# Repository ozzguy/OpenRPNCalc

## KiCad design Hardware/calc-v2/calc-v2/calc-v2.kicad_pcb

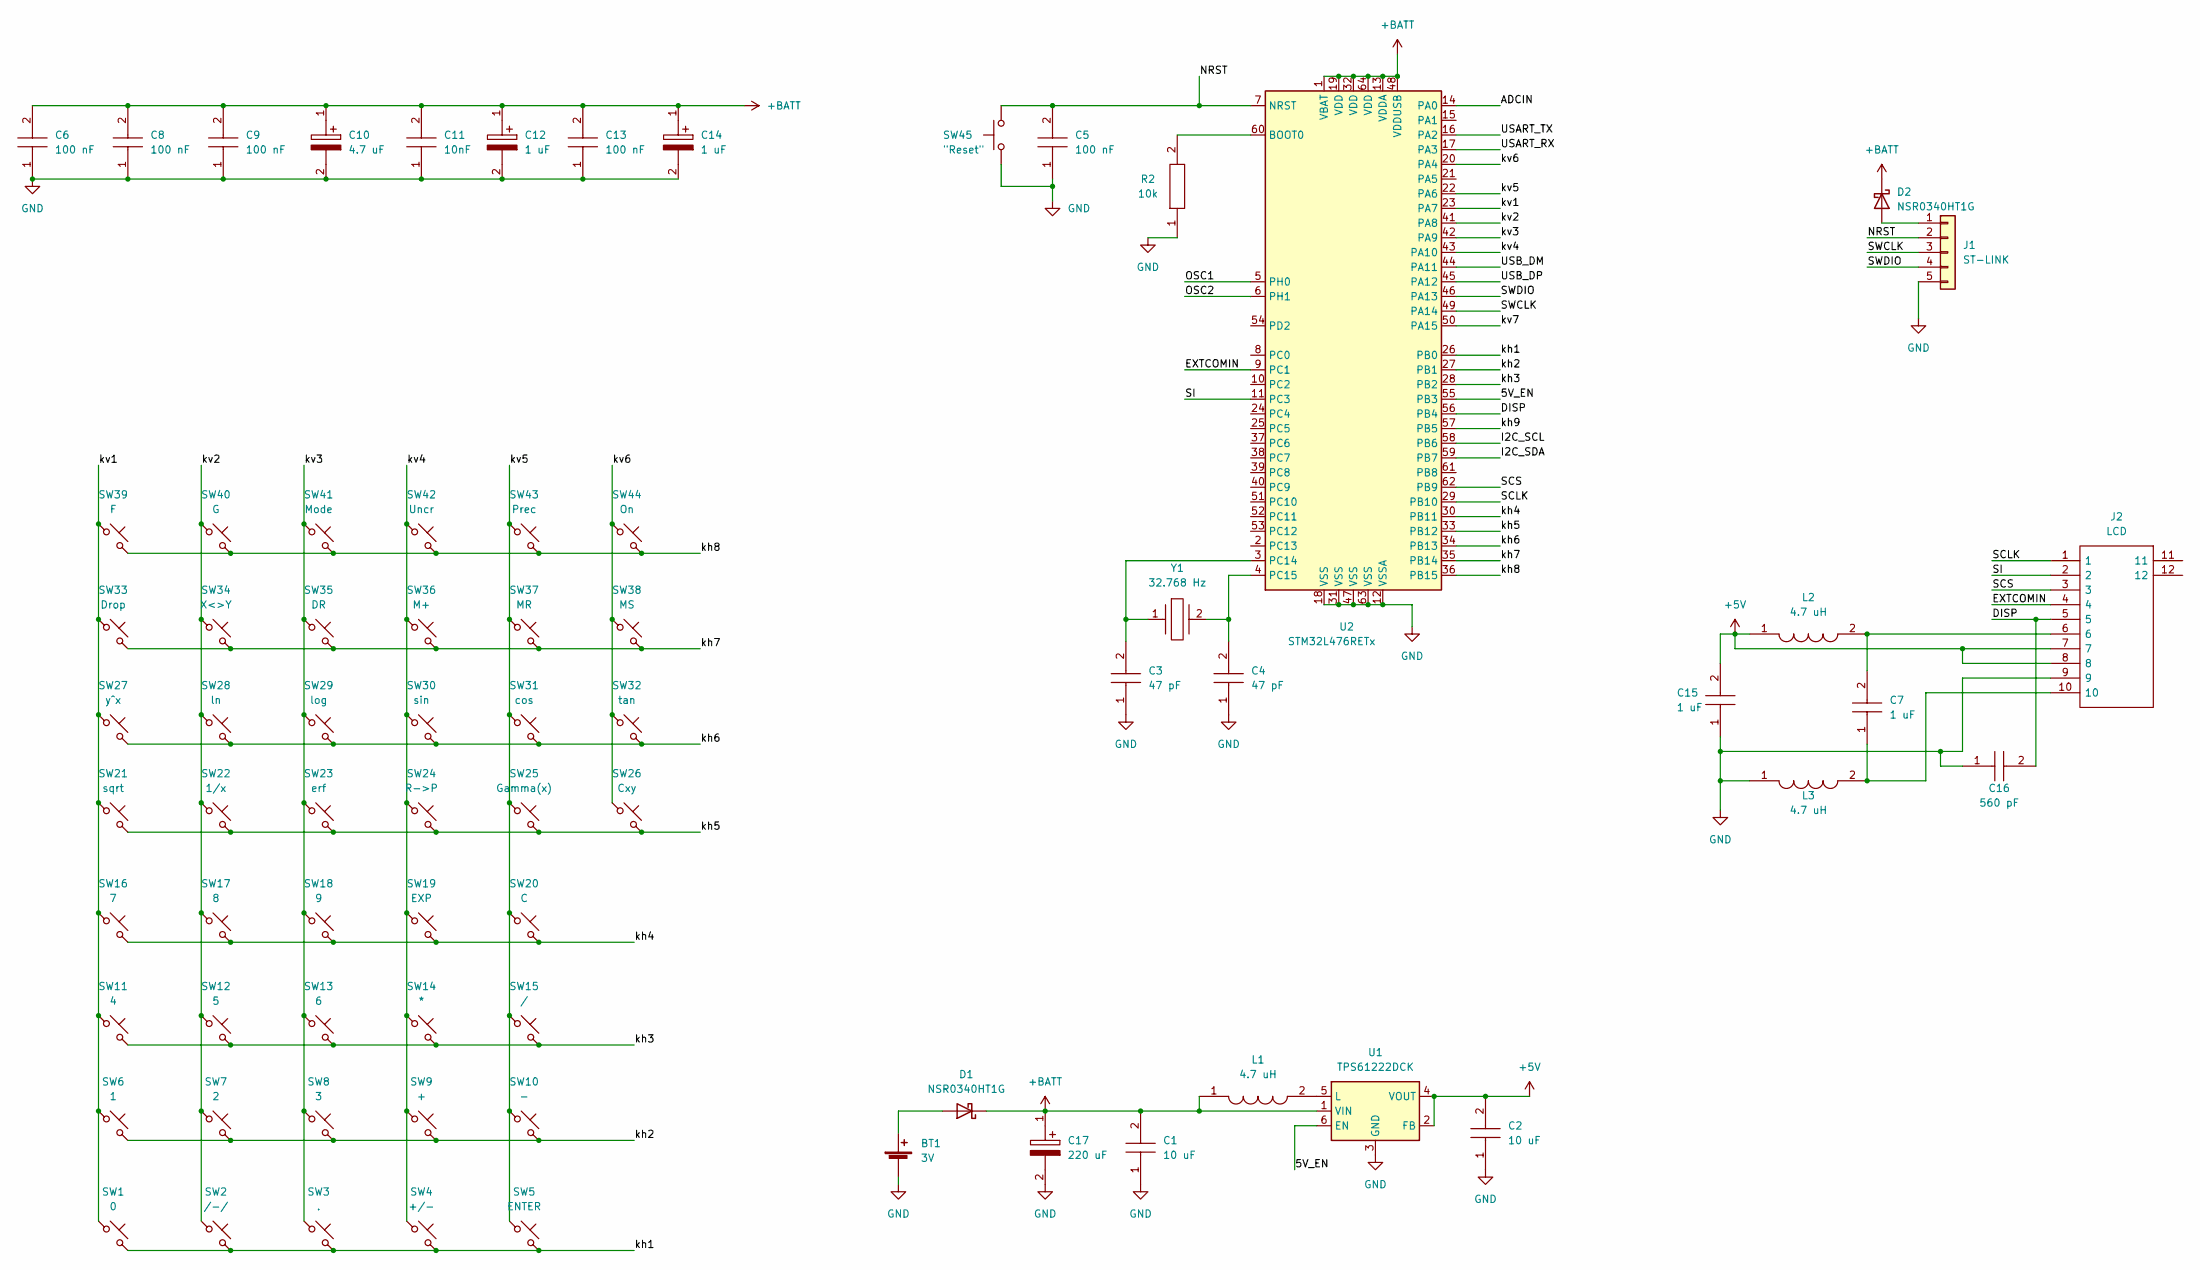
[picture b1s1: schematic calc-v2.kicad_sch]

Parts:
BT1: 3V; BatteryHolder_Keystone_1057_1x2032
C1, C2: 10 uF; C_0603_1608Metric_Pad1.08x0.95mm_HandSolder; Mouser Part Number 963-JMK107ABJ106MA-T
C3, C4: 47 pF; C_0603_1608Metric_Pad1.08x0.95mm_HandSolder; Mouser Part Number 581-06036A470KAT2A
C5, C6, C8, C9, C13: 100 nF; C_0603_1608Metric_Pad1.08x0.95mm_HandSolder; Mouser Part Number 581-06036C104MAZ2A
C7, C15: 1 uF; C_0603_1608Metric_Pad1.08x0.95mm_HandSolder; Mouser Part Number 710-885012106003
C10: 4.7 uF; C_0603_1608Metric_Pad1.08x0.95mm_HandSolder; Mouser Part Number 581-TPCL475K010R5000
C11: 10nF; C_0603_1608Metric_Pad1.08x0.95mm_HandSolder; Mouser Part Number 810-CGA3E2C0G1H103J
C12, C14: 1 uF; C_0603_1608Metric_Pad1.08x0.95mm_HandSolder; Mouser Part Number 581-TACL105K006X
C16: 560 pF; C_0603_1608Metric_Pad1.08x0.95mm_HandSolder; Mouser Part Number 80-C0603C561F4GAUTO
C17: 220 uF; CAPPM3528X210N; Mouser Part Number 647-F930J227KBA
D1, D2: NSR0340HT1G; D_SOD-323_HandSoldering
J1: ST-LINK; PinHeader_1x05_P2.54mm_Horizontal
J2: LCD; FH2810S05SH11; Mouser Part Number 798-FH2810S05SH11
L1, L2, L3: 4.7 uH; L_0805_2012Metric_Pad1.15x1.40mm_HandSolder; Manufacturer_Part_Number L0805C4R7MDWIT
R2: 10k; C_0603_1608Metric_Pad1.08x0.95mm_HandSolder; Mouser Part Number 652-CMP0603AFX-1002L
SW1: 0; SW_SPST_EVQQ2
SW2: /-/; SW_SPST_EVQQ2
SW3: .; SW_SPST_EVQQ2
SW4: +/-; SW_SPST_EVQQ2
SW5: ENTER; SW_SPST_EVQQ2
SW6: 1; SW_SPST_EVQQ2
SW7: 2; SW_SPST_EVQQ2
SW8: 3; SW_SPST_EVQQ2
SW9: +; SW_SPST_EVQQ2
SW10: -; SW_SPST_EVQQ2
SW11: 4; SW_SPST_EVQQ2
SW12: 5; SW_SPST_EVQQ2
SW13: 6; SW_SPST_EVQQ2
SW14: *; SW_SPST_EVQQ2
SW15: /; SW_SPST_EVQQ2
SW16: 7; SW_SPST_EVQQ2
SW17: 8; SW_SPST_EVQQ2
SW18: 9; SW_SPST_EVQQ2
SW19: EXP; SW_SPST_EVQQ2
SW20: C; SW_SPST_EVQQ2
SW21: sqrt; SW_SPST_EVQQ2
SW22: 1/x; SW_SPST_EVQQ2
SW23: erf; SW_SPST_EVQQ2
SW24: R->P; SW_SPST_EVQQ2
SW25: Gamma(x); SW_SPST_EVQQ2
SW26: Cxy; SW_SPST_EVQQ2
SW27: y^x; SW_SPST_EVQQ2
SW28: ln; SW_SPST_EVQQ2
SW29: log; SW_SPST_EVQQ2
SW30: sin; SW_SPST_EVQQ2
SW31: cos; SW_SPST_EVQQ2
SW32: tan; SW_SPST_EVQQ2
SW33: Drop; SW_SPST_EVQQ2
SW34: X<>Y; SW_SPST_EVQQ2
SW35: DR; SW_SPST_EVQQ2
SW36: M+; SW_SPST_EVQQ2
SW37: MR; SW_SPST_EVQQ2
SW38: MS; SW_SPST_EVQQ2
SW39: F; SW_SPST_EVQQ2
SW40: G; SW_SPST_EVQQ2
SW41: Mode; SW_SPST_EVQQ2
SW42: Uncr; SW_SPST_EVQQ2
SW43: Prec; SW_SPST_EVQQ2
SW44: On; SW_SPST_EVQQ2
SW45: "Reset"; SW_SPST_EVQQ2
U1: TPS61222DCK; Texas_R-PDSO-G6
U2: STM32L476RETx; LQFP-64_10x10mm_P0.5mm
Y1: 32.768 Hz; 9HT1132768KDZBT; Mouser Part Number 717-9HT11-32.76KDZBT

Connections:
+5V: C2.2, C15.2, J2.7, J2.8, L2.1, U1.2 (FB), U1.4 (VOUT)
+BATT: C1.2, C6.2, C8.2, C9.2, C10.1, C11.2, C12.1, C13.2, C14.1, C17.1, D1.1 (K), D2.1 (K), L1.1, U1.1 (VIN), U2.1 (VBAT), U2.13 (VDDA), U2.19 (VDD), U2.32 (VDD), U2.48 (VDDUSB), U2.64 (VDD)
/5V_EN: U1.6 (EN), U2.55 (PB3)
/ADCIN: U2.14 (PA0)
/DISP: C16.2, J2.5, U2.56 (PB4)
/EXTCOMIN: J2.4, U2.9 (PC1)
/I2C_SCL: U2.58 (PB6)
/I2C_SDA: U2.59 (PB7)
/NRST: C5.2, J1.2, SW45.2, U2.7 (NRST)
/OSC1: U2.5 (PH0)
/OSC2: U2.6 (PH1)
/SCLK: J2.1, U2.29 (PB10)
/SCS: J2.3, U2.62 (PB9)
/SI: J2.2, U2.11 (PC3)
/SWCLK: J1.3, U2.49 (PA14)
/SWDIO: J1.4, U2.46 (PA13)
/USART_RX: U2.17 (PA3)
/USART_TX: U2.16 (PA2)
/USB_DM: U2.44 (PA11)
/USB_DP: U2.45 (PA12)
/kh1: SW1.2, SW2.2, SW3.2, SW4.2, SW5.2, U2.26 (PB0)
/kh2: SW6.2, SW7.2, SW8.2, SW9.2, SW10.2, U2.27 (PB1)
/kh3: SW11.2, SW12.2, SW13.2, SW14.2, SW15.2, U2.28 (PB2)
/kh4: SW16.2, SW17.2, SW18.2, SW19.2, SW20.2, U2.30 (PB11)
/kh5: SW21.2, SW22.2, SW23.2, SW24.2, SW25.2, SW26.2, U2.33 (PB12)
/kh6: SW27.2, SW28.2, SW29.2, SW30.2, SW31.2, SW32.2, U2.34 (PB13)
/kh7: SW33.2, SW34.2, SW35.2, SW36.2, SW37.2, SW38.2, U2.35 (PB14)
/kh8: SW39.2, SW40.2, SW41.2, SW42.2, SW43.2, SW44.2, U2.36 (PB15)
/kh9: U2.57 (PB5)
/kv1: SW1.1, SW6.1, SW11.1, SW16.1, SW21.1, SW27.1, SW33.1, SW39.1, U2.23 (PA7)
/kv2: SW2.1, SW7.1, SW12.1, SW17.1, SW22.1, SW28.1, SW34.1, SW40.1, U2.41 (PA8)
/kv3: SW3.1, SW8.1, SW13.1, SW18.1, SW23.1, SW29.1, SW35.1, SW41.1, U2.42 (PA9)
/kv4: SW4.1, SW9.1, SW14.1, SW19.1, SW24.1, SW30.1, SW36.1, SW42.1, U2.43 (PA10)
/kv5: SW5.1, SW10.1, SW15.1, SW20.1, SW25.1, SW31.1, SW37.1, SW43.1, U2.22 (PA6)
/kv6: SW26.1, SW32.1, SW38.1, SW44.1, U2.20 (PA4)
/kv7: U2.50 (PA15)
GND: BT1.2 (-), C1.1, C2.1, C3.1, C4.1, C5.1, C6.1, C8.1, C9.1, C10.2, C11.1, C12.2, C13.1, C14.2, C15.1, C16.1, C17.2, J1.5, J2.9, L3.1, R2.1, SW45.1, U1.3 (GND), U2.12 (VSSA), U2.18 (VSS), U2.31 (VSS), U2.47 (VSS), U2.63 (VSS)
unnamed: BT1.1 (+), D1.2 (A)
unnamed: C3.2, U2.3 (PC14), Y1.1
unnamed: C4.2, U2.4 (PC15), Y1.2
unnamed: C7.1, J2.10, L3.2
unnamed: C7.2, J2.6, L2.2
unnamed: D2.2 (A), J1.1
unnamed: L1.2, U1.5 (L)
unnamed: R2.2, U2.60 (BOOT0)

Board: 2 copper layers, 74 parts (30 on the bottom side), 34 nets, no tracks yet.

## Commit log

2022-11-24 Initial schematic overhaul commit
2022-11-24 Made all footprints handsolder-friendly
2022-11-24 Added .gitignore
2022-11-24 Created 3D models for the EVQ switches
2022-11-25 Created 3D model for Keystone 1057. Updated Molex footprint to hand-solder-friendly. Created 3D model for LS027 Screen.
2022-12-08 started case creation
